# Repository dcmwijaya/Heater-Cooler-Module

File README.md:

# Heater-Cooler Module
<strong>Elective Class Final Project: PCB Design</strong><br>

In this PCB project, I created a simple IoT trainer design that includes the relationship between sensors and actuators. The assigned sensor is LM35, while the assigned actuator is Fan.

<br><br>

## Appreciation
If this work is useful to you, then support this work as a form of appreciation to the author by clicking the ``` ⭐Star ``` button at the top of the repository.

<br><br>

## LICENSE
MIT License - Copyright © 2023 - Devan C. M. Wijaya, S.Kom

Permission is hereby granted without charge to any person obtaining a copy of this software and the software-related documentation files to deal in them without restriction, including without limitation the right to use, copy, modify, merge, publish, distribute, sublicense, and/or sell copies of the Software, and to permit persons receiving the Software to be furnished therewith on the following terms:

The above copyright notice and this permission notice must accompany all copies or substantial portions of the Software.

IN ANY EVENT, THE AUTHOR OR COPYRIGHT HOLDER HEREIN RETAINS FULL OWNERSHIP RIGHTS. THE SOFTWARE IS PROVIDED AS IS, WITHOUT WARRANTY OF ANY KIND, EITHER EXPRESS OR IMPLIED, THEREFORE IF ANY DAMAGE, LOSS, OR OTHERWISE ARISES FROM THE USE OR OTHER DEALINGS IN THE SOFTWARE, THE AUTHOR OR COPYRIGHT HOLDER SHALL NOT BE LIABLE, AS THE USE OF THE SOFTWARE IS NOT COMPELLED AT ALL, SO THE RISK IS YOUR OWN.

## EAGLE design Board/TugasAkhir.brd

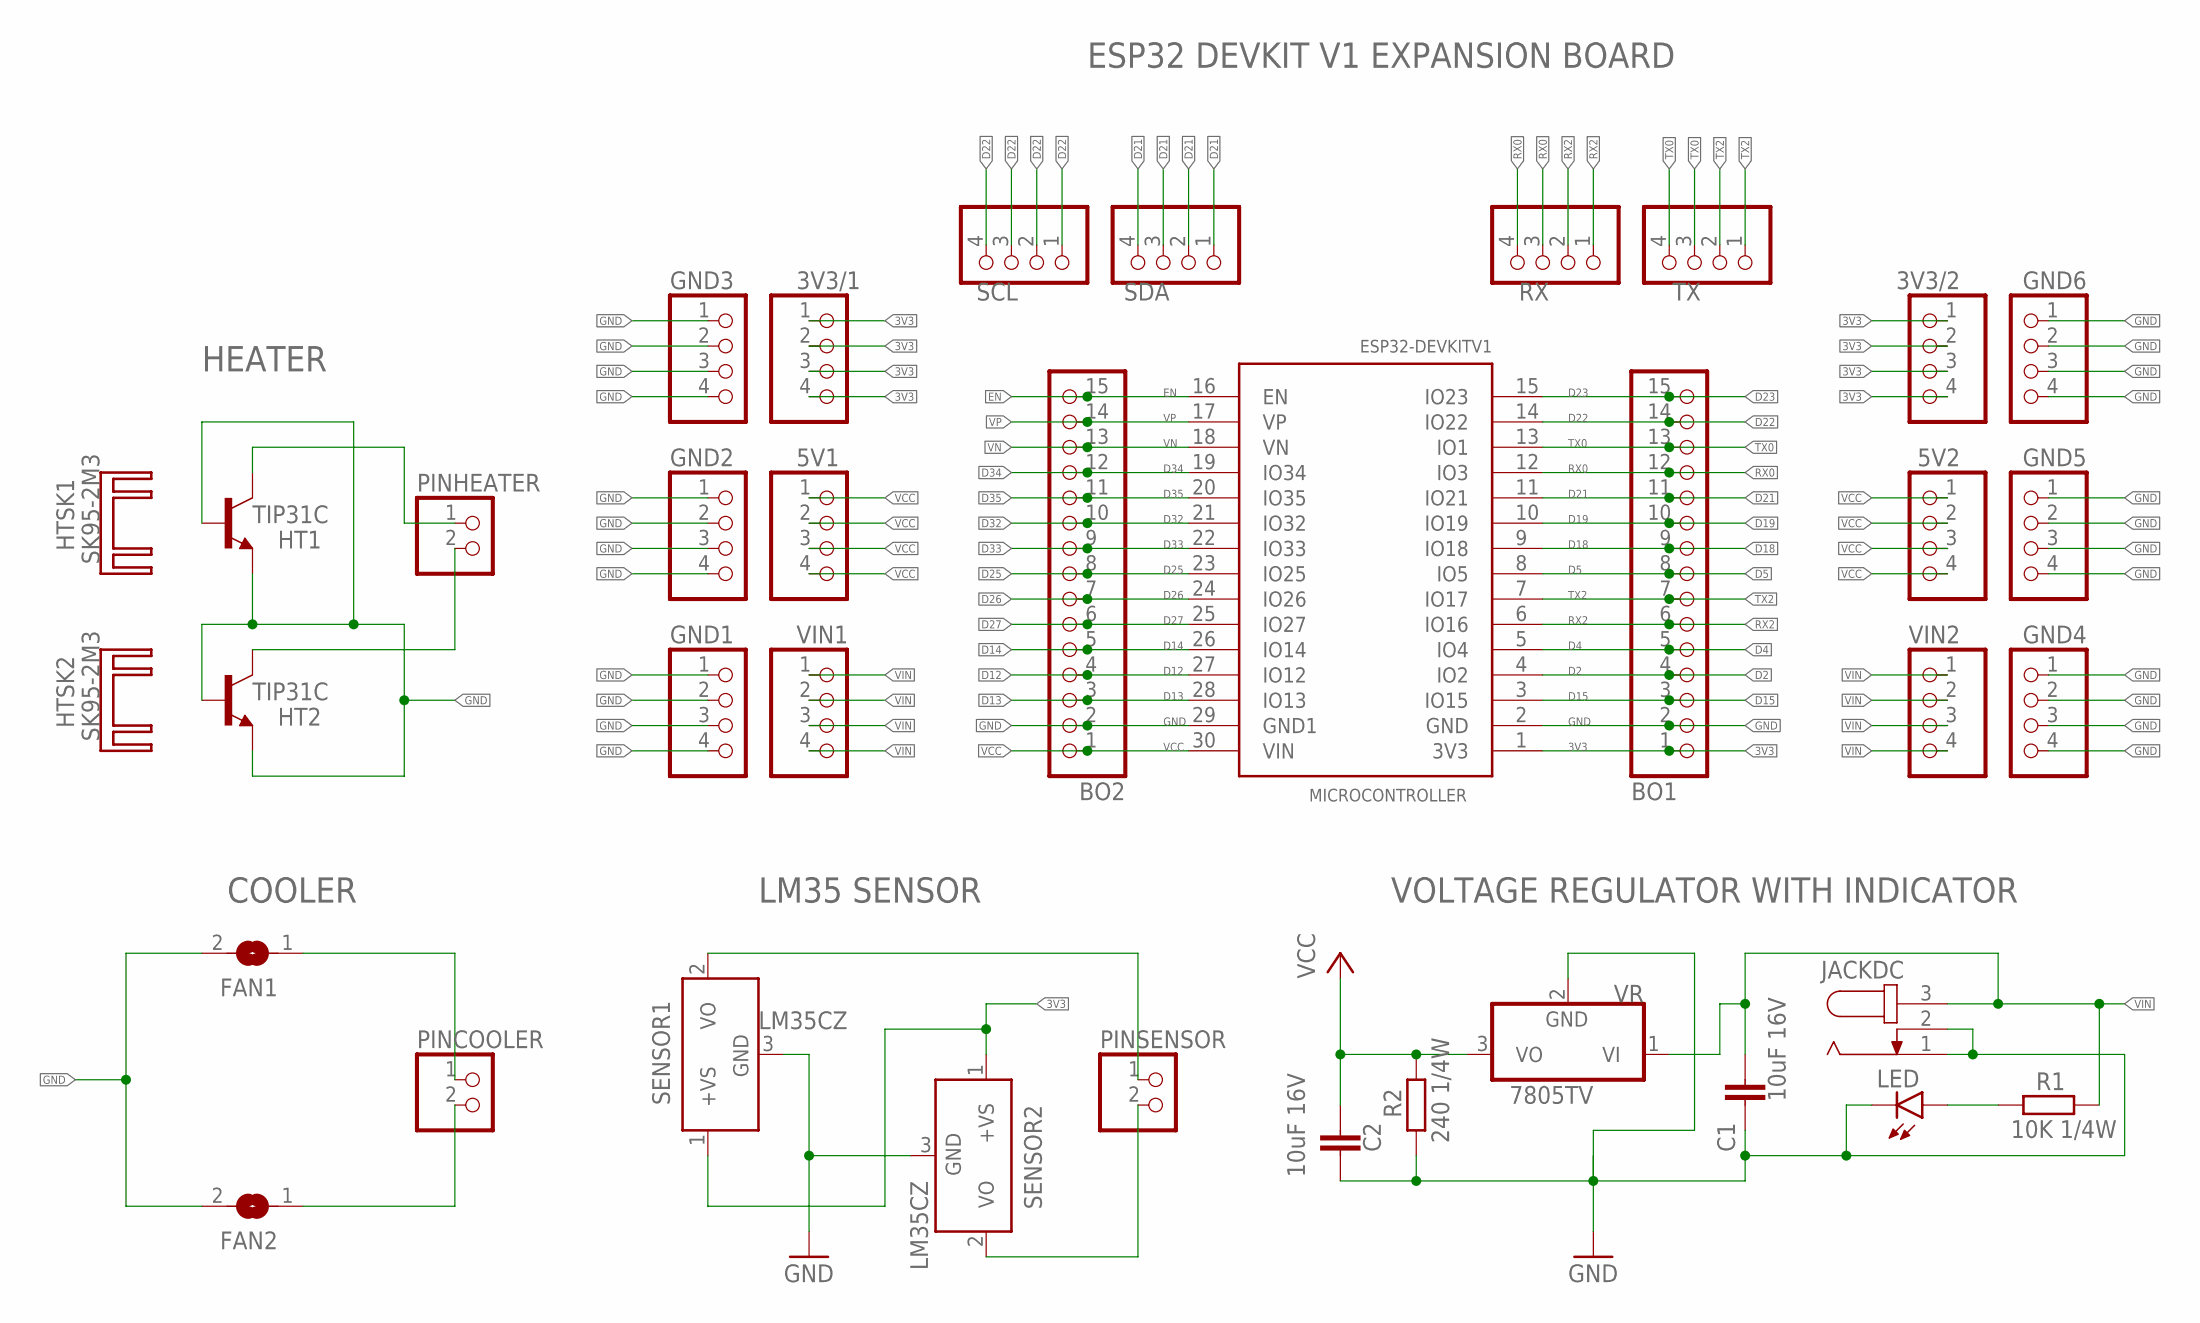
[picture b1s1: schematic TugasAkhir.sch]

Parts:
3V3/1, 3V3/2, 5V1, 5V2: PINHD-1X4; 1X04
BO1, BO2: PINHD-1X15; 1X15
C1, C2: 10uF 16V; C1206K
FAN1, FAN2: SJW
GND1, GND2, GND3, GND4, GND5, GND6: PINHD-1X4; 1X04
HT1, HT2: TIP31C; TO220
HTSK1, HTSK2: SK95-2M3
JACKDC: JACK-PLUG1; SPC4078
LED: LEDB155; Q62902-B155
MICROCONTROLLER: ESP32DEVKITV1; ESP32-DEVKITV1
PINCOOLER: PINHD-1X2; 1X02
PINHEATER: PINHD-1X2; 1X02
PINSENSOR: PINHD-1X2; 1X02
R1: 10K 1/4W; M1206
R2: 240 1/4W; M1206
RX: PINHD-1X4; 1X04
SCL: PINHD-1X4; 1X04
SDA: PINHD-1X4; 1X04
SENSOR1, SENSOR2: LM35CZ; TO92
TX: PINHD-1X4; 1X04
VIN1, VIN2: PINHD-1X4; 1X04
VR: 7805TV; TO220V

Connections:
3V3: 3V3/1.1, 3V3/1.2, 3V3/1.3, 3V3/1.4, 3V3/2.1, 3V3/2.2, 3V3/2.3, 3V3/2.4, BO1.1, MICROCONTROLLER.1 (3V3), SENSOR1.1 (+VS), SENSOR2.1 (+VS)
D2: BO1.4, MICROCONTROLLER.4 (IO2)
D4: BO1.5, MICROCONTROLLER.5 (IO4)
D5: BO1.8, MICROCONTROLLER.8 (IO5)
D12: BO2.4, MICROCONTROLLER.27 (IO12)
D13: BO2.3, MICROCONTROLLER.28 (IO13)
D14: BO2.5, MICROCONTROLLER.26 (IO14)
D15: BO1.3, MICROCONTROLLER.3 (IO15)
D18: BO1.9, MICROCONTROLLER.9 (IO18)
D19: BO1.10, MICROCONTROLLER.10 (IO19)
D21: BO1.11, MICROCONTROLLER.11 (IO21), SDA.1, SDA.2, SDA.3, SDA.4
D22: BO1.14, MICROCONTROLLER.14 (IO22), SCL.1, SCL.2, SCL.3, SCL.4
D23: BO1.15, MICROCONTROLLER.15 (IO23)
D25: BO2.8, MICROCONTROLLER.23 (IO25)
D26: BO2.7, MICROCONTROLLER.24 (IO26)
D27: BO2.6, MICROCONTROLLER.25 (IO27)
D32: BO2.10, MICROCONTROLLER.21 (IO32)
D33: BO2.9, MICROCONTROLLER.22 (IO33)
D34: BO2.12, MICROCONTROLLER.19 (IO34)
D35: BO2.11, MICROCONTROLLER.20 (IO35)
EN: BO2.15, MICROCONTROLLER.16 (EN)
GND: BO1.2, BO2.2, C1.2, C2.2, FAN1.2, FAN2.2, GND1.1, GND1.2, GND1.3, GND1.4, GND2.1, GND2.2, GND2.3, GND2.4, GND3.1, GND3.2, GND3.3, GND3.4, GND4.1, GND4.2, GND4.3, GND4.4, GND5.1, GND5.2, GND5.3, GND5.4, GND6.1, GND6.2, GND6.3, GND6.4, HT1.1 (B), HT1.3 (E), HT2.1 (B), HT2.3 (E), JACKDC.1, JACKDC.2, LED.K (C), MICROCONTROLLER.2 (GND), MICROCONTROLLER.29 (GND1), R2.1, SENSOR1.3 (GND), SENSOR2.3 (GND), VR.2 (GND)
INF1: FAN1.1, PINCOOLER.1
INF2: FAN2.1, PINCOOLER.2
INH1: HT1.2 (C), PINHEATER.1
INH2: HT2.2 (C), PINHEATER.2
INL1: PINSENSOR.1, SENSOR1.2 (VO)
INL2: PINSENSOR.2, SENSOR2.2 (VO)
RX0: BO1.12, MICROCONTROLLER.12 (IO3), RX.3, RX.4
RX2: BO1.6, MICROCONTROLLER.6 (IO16), RX.1, RX.2
TX0: BO1.13, MICROCONTROLLER.13 (IO1), TX.3, TX.4
TX2: BO1.7, MICROCONTROLLER.7 (IO17), TX.1, TX.2
VCC: 5V1.1, 5V1.2, 5V1.3, 5V1.4, 5V2.1, 5V2.2, 5V2.3, 5V2.4, BO2.1, C2.1, MICROCONTROLLER.30 (VIN), R2.2, VR.3 (VO)
VIN: C1.1, JACKDC.3, R1.2, VIN1.1, VIN1.2, VIN1.3, VIN1.4, VIN2.1, VIN2.2, VIN2.3, VIN2.4, VR.1 (VI)
VN: BO2.13, MICROCONTROLLER.18 (VN)
VOUT: LED.A, R1.1
VP: BO2.14, MICROCONTROLLER.17 (VP)

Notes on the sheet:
LM35 SENSOR
ESP32 DEVKIT V1 EXPANSION BOARD
VOLTAGE REGULATOR WITH INDICATOR
HEATER
COOLER

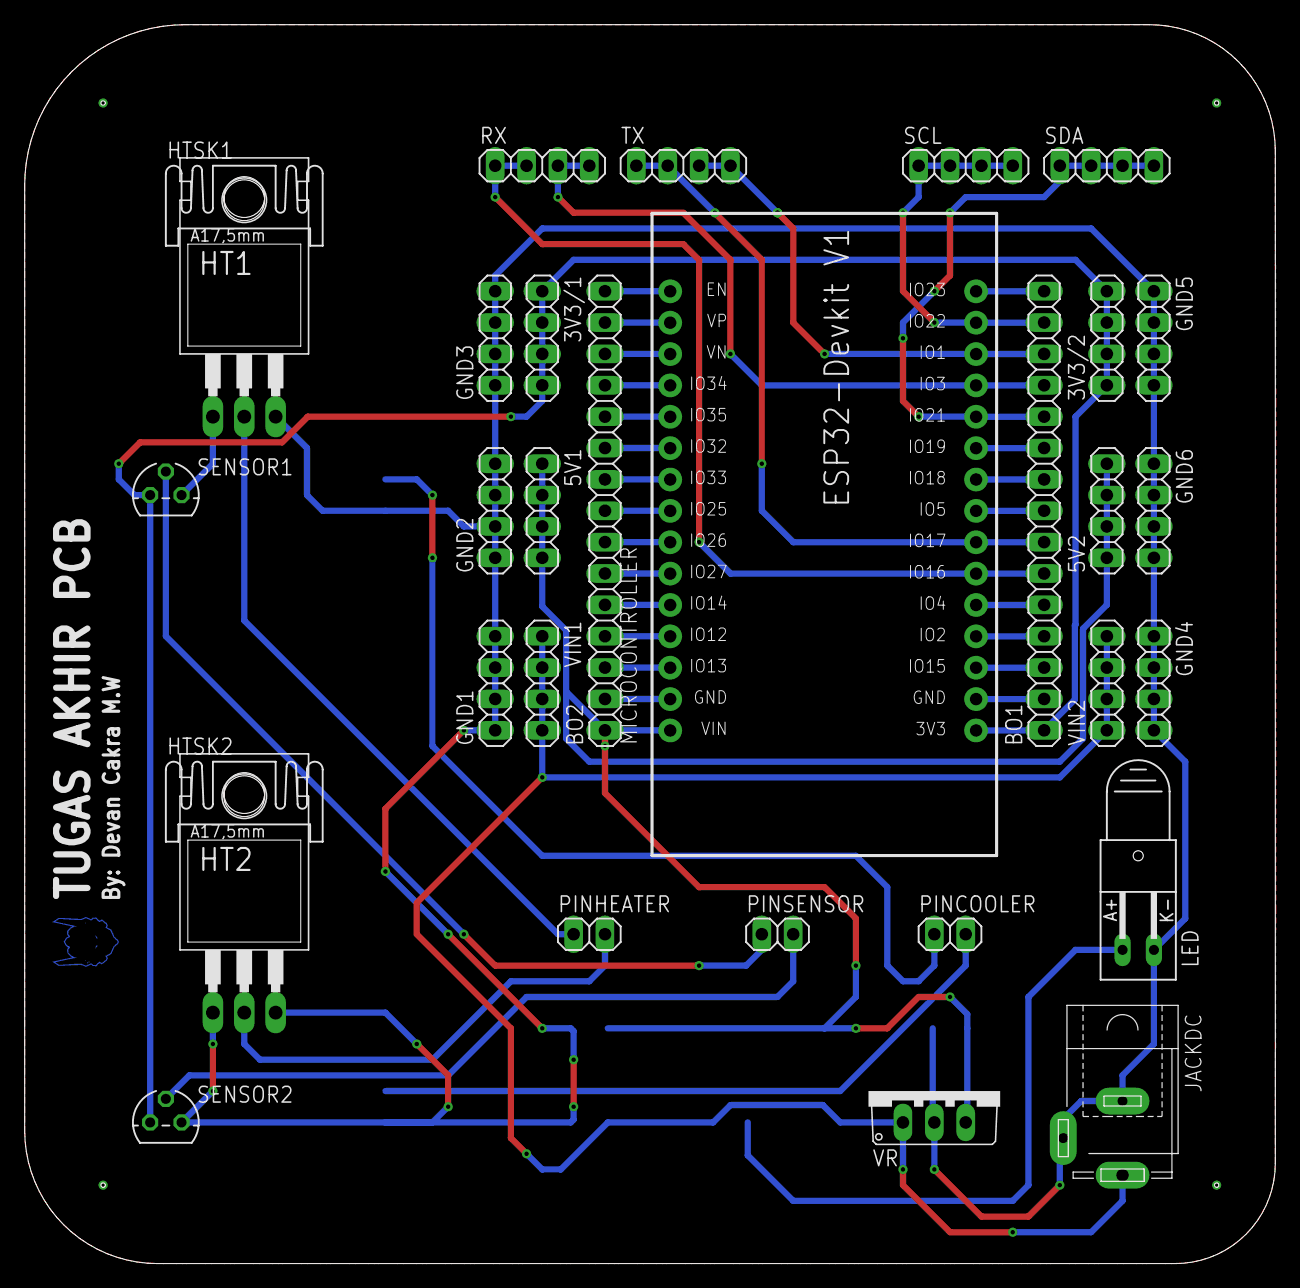
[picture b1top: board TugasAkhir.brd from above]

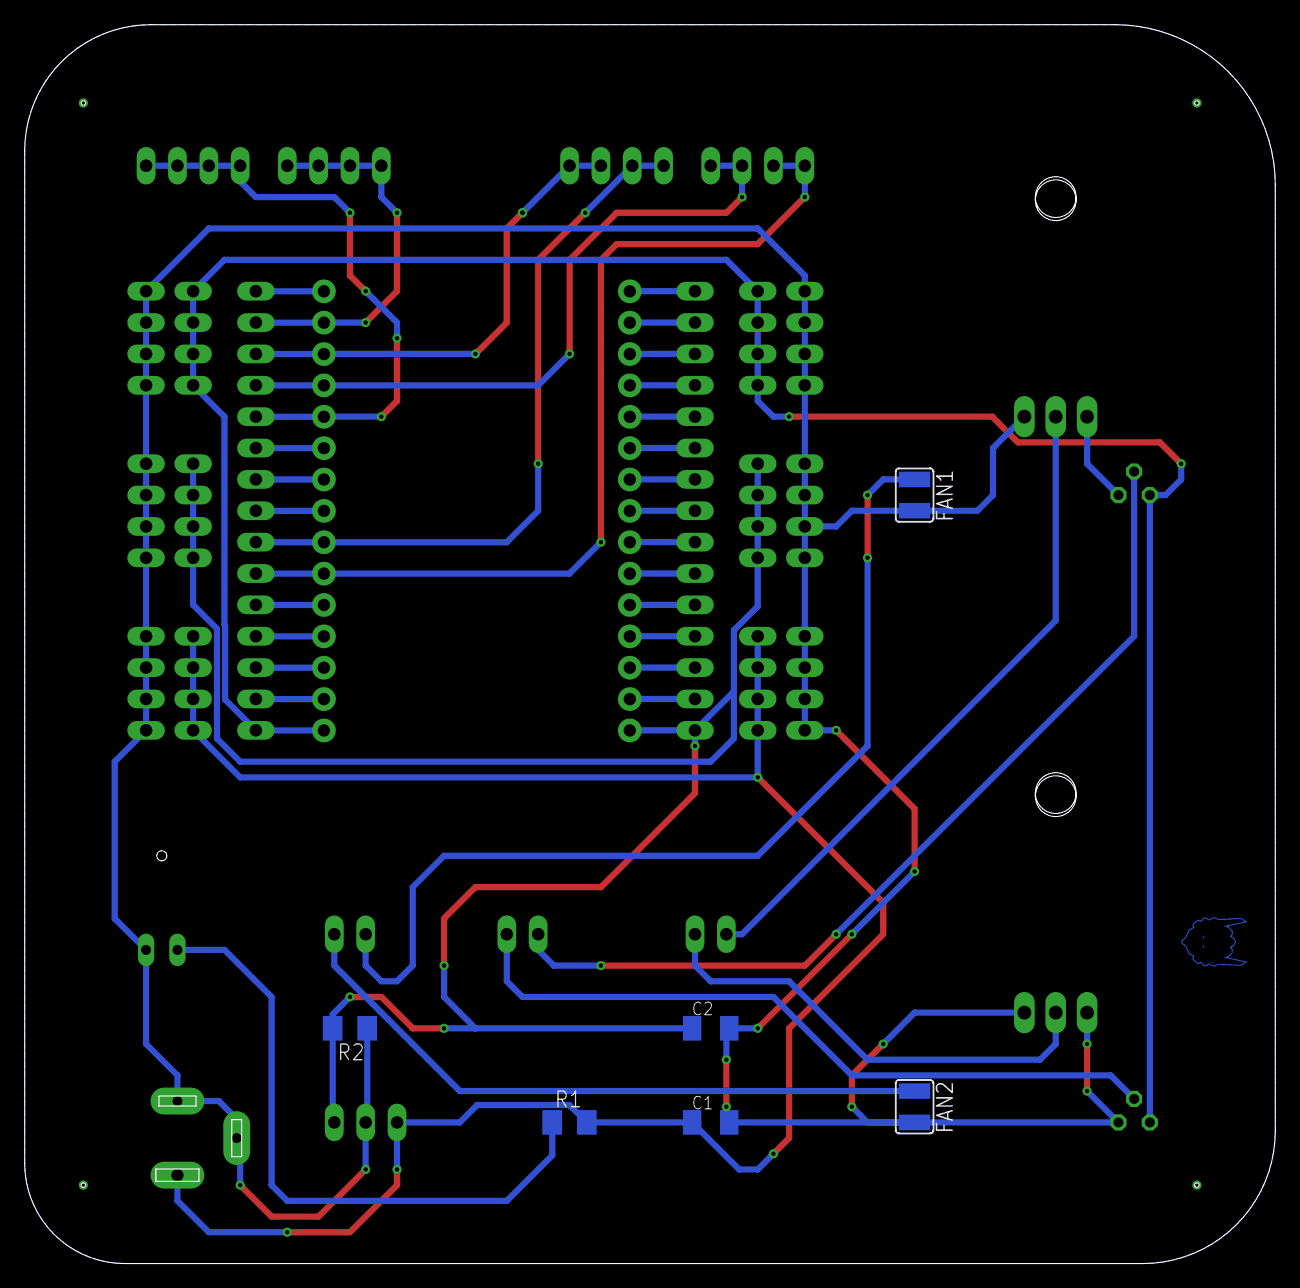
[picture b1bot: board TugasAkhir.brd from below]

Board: 2 copper layers, 101.3 x 100.3 mm, 37 parts (6 on the bottom side), 37 nets.

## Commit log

2023-01-08 Add: All Files
2023-01-08 Add: Gerber
2023-01-08 Add: Report PDF
2024-02-01 Update LICENSE
2024-10-03 Update: 03/10/2024
